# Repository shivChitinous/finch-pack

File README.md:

# finch-pack

[Rajan Lab](http://www.iiserpune.ac.in/~raghav/) PCB to record and amplify respiratory pressure in adult zebra finches

in communication with [Dr. Lena Veit (UCSF)](https://profiles.ucsf.edu/lena.veit) and [Umesh Mohan (NCBS)](https://gitlab.com/umesh-NCBS/bird-backpack-example)

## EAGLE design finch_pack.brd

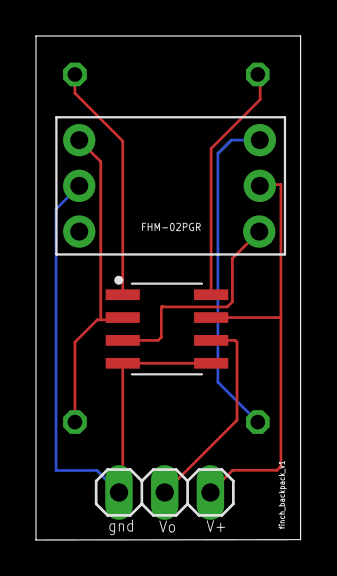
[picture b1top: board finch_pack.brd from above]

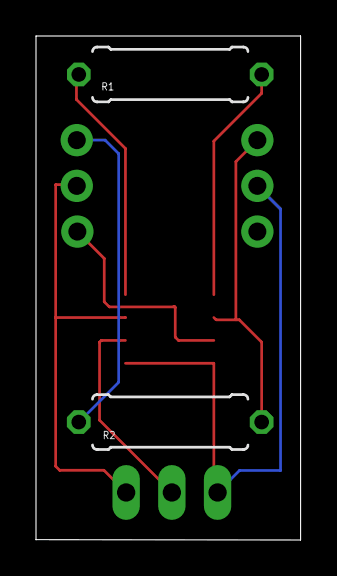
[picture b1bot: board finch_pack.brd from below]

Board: 2 copper layers, 14.7 x 28.0 mm, 5 parts (2 on the bottom side), 8 nets.

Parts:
CONNECTOR: 1X03
FHM-02PGR: FHM-02PGR
INA122UA: INA122UA
R1: 2200; 0309/10
R2: 100; 0309/10

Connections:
GND: CONNECTOR.3, FHM-02PGR.5, INA122UA.4, INA122UA.5
unnamed: FHM-02PGR.3, INA122UA.3
unnamed: FHM-02PGR.6, INA122UA.2, R2.2
unnamed: FHM-02PGR.1, R2.1
unnamed: INA122UA.1, R1.1
unnamed: INA122UA.8, R1.2
V+: CONNECTOR.1, FHM-02PGR.2, INA122UA.7
VO: CONNECTOR.2, INA122UA.6

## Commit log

2020-01-30 board files
2020-01-30 datasheets
2020-01-30 pressure sensor library
2020-01-30 amplifier library
2020-01-30 schematic files
2020-01-30 description
2020-01-30 eagle file
2020-01-30 gerber files
2020-01-30 Update DESCRIPTION
2020-01-30 eagle project file
2020-01-30 assembly, drilling, gerber files
2020-01-30 A4 print
2020-01-30 board file
2020-01-30 schematic file
2020-01-31 assembly, drilling and gerber files
2020-01-31 pressure transducer library
2020-01-31 pressure sensory library
2020-02-01 A4 sheet
2020-02-04 project file
